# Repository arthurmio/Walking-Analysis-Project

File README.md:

# Walking-Analysis-Project
Projet d'analyse de la marche réalisé par :
  - GOURDON Mathéo
  - MARIANO Arthur 
  - TRIGUI Ianis

Ce projet a été développé dans le cadre du projet "Fil Rouge" en 5ème année à l'ESIEE Paris.  
Ce prototype d'analyse propose une solution d'analyse de la marche sans fil à l'aide d'Arduinos 33 BLE et de capteurs inertiels (BNO005) connectées grâce au protocole BLE (Bluetooth Low Energy). La lecture et l'interprétation des données sont réalisées à l'aide d'une interface sous Python.

# How to use it
Afin d'utiliser correctement le prototype veuillez vous référer à la notice d'utilisation dans le répertoire "Documentation".

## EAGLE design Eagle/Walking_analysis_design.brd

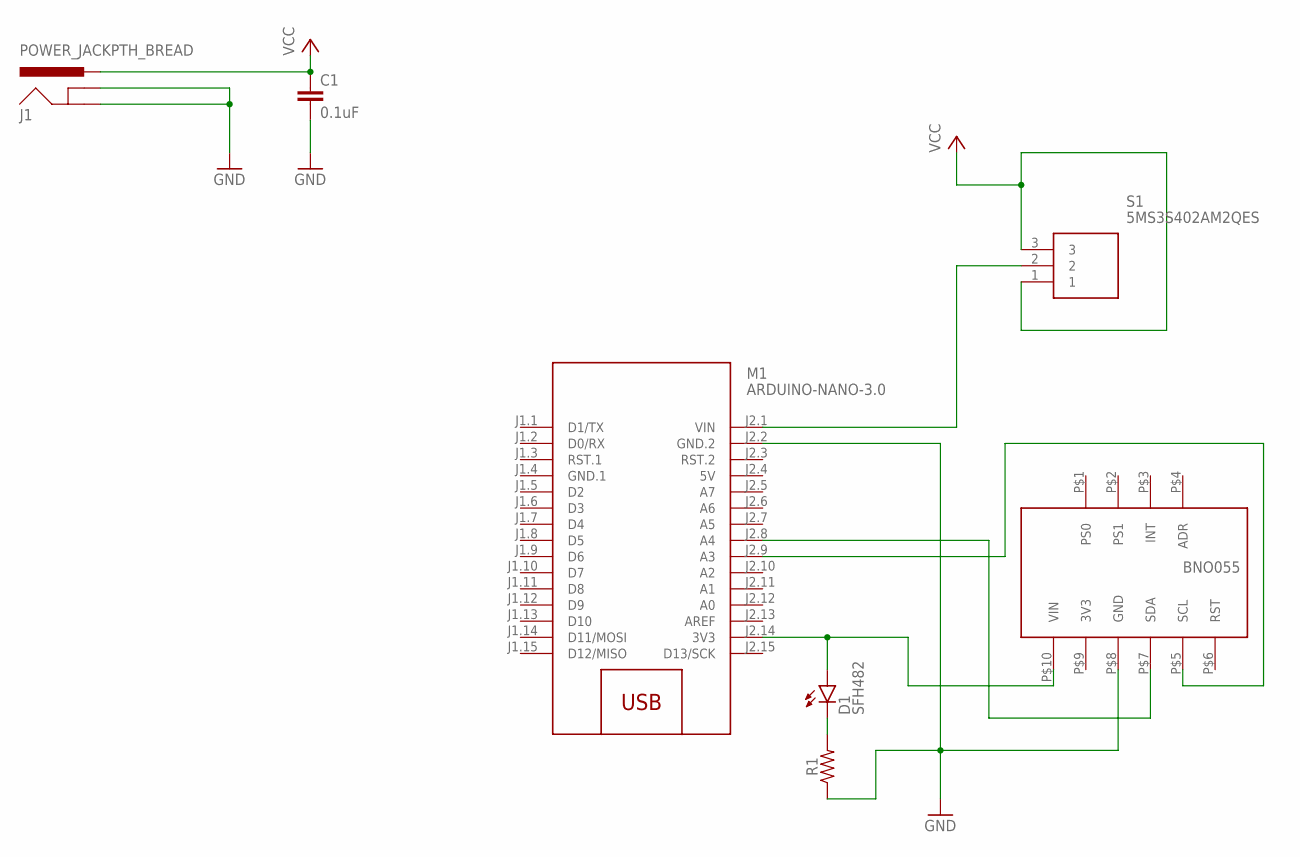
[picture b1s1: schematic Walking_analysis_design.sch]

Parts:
C1: 0.1uF; CAP-PTH-SMALL-KIT
D1: SFH482
J1: POWER_JACKPTH_BREAD; POWER_JACK_PTH_BREAD
M1: ARDUINO-NANO-3.0
R1: AXIAL-0.3
S1: 5MS3S402AM2QES
U$1: BNO055; BNO055_FOOTPRINT

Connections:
3V3: U$1.P$9 (3V3)
5V: M1.J2.4 (5V)
GND: C1.2, J1.GND, J1.GNDBREAK, M1.J2.2 (GND.2), R1.P$1 (1), U$1.P$8 (GND)
GND.1: M1.J1.4 (GND.1)
unnamed: M1.J2.8 (A4), U$1.P$7 (SDA)
unnamed: M1.J2.9 (A3), U$1.P$5 (SCL)
unnamed: D1.A, M1.J2.14 (3V3), U$1.P$10 (VIN)
unnamed: M1.J2.1 (VIN), S1.2
unnamed: D1.K (C), R1.P$2 (2)
VCC: C1.1, J1.PWR, S1.1, S1.3

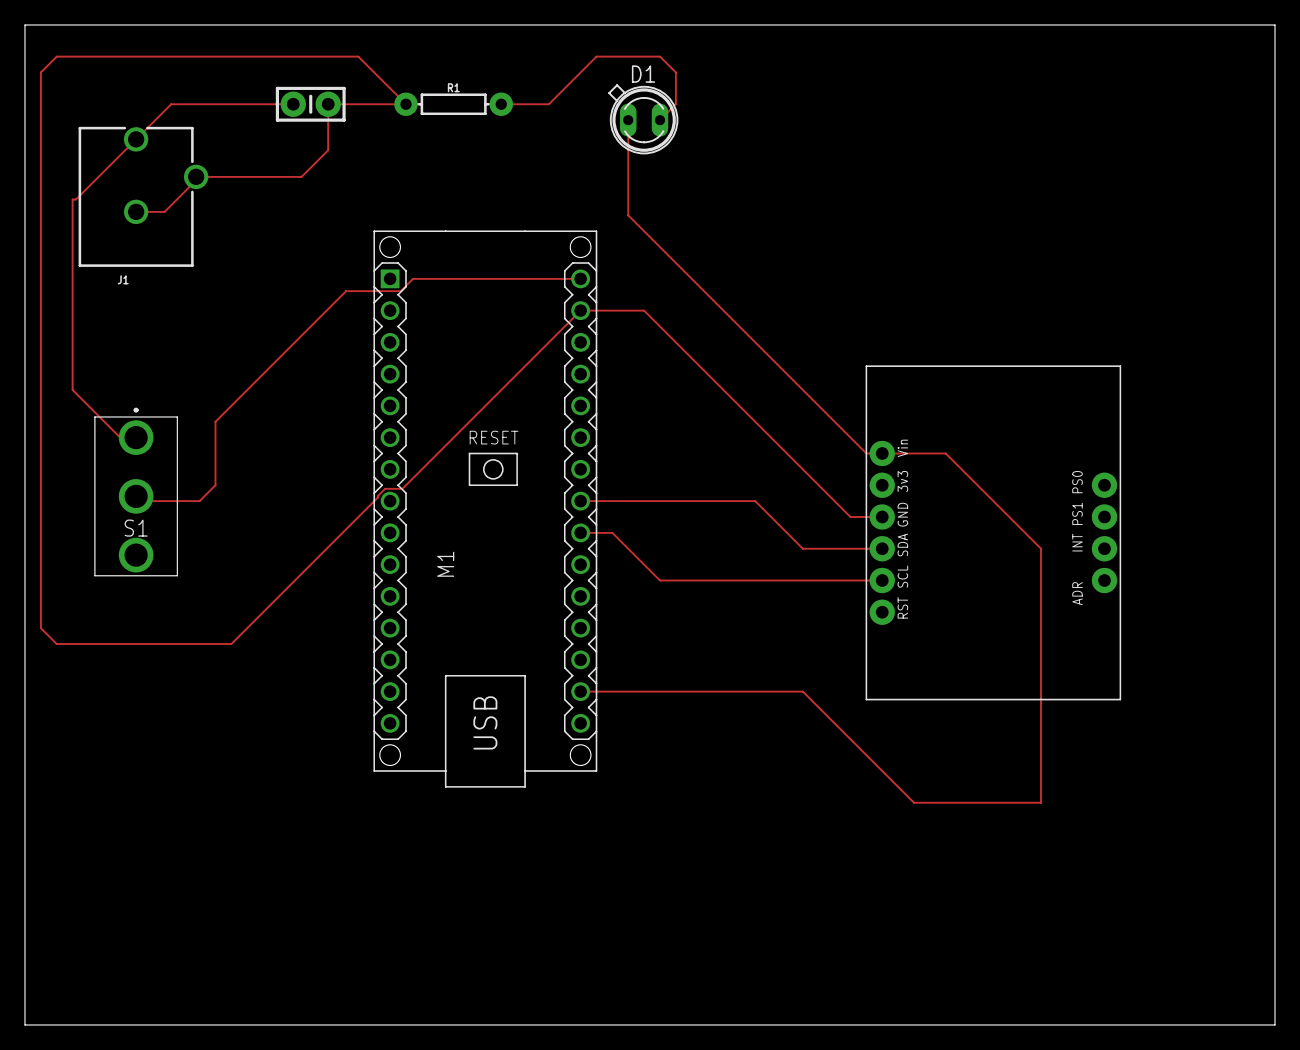
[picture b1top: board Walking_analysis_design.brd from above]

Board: 2 copper layers, 100.0 x 80.0 mm, 7 parts (0 on the bottom side), 7 nets.

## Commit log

2021-01-19 Creation of Arduino and Python repository
2021-01-19 File for git command
2021-03-18 Branch python created for interface
2021-03-18 Decoupage code
2021-03-19 Matplotlib added
2021-03-19 Arduino BLE connection
2021-03-24 Arduino data connected to python
2021-03-24 Correction of BN055_euler for serial interface
2021-03-26 Graphic created for yaw/pitch/roll in real time
2021-03-31 Data saved in a file + plot of this data
2021-03-31 Data save + plot for all arduino
2021-04-02 Update of interface for plot
2021-04-02 Interface with different windows
2021-04-06 Final interface
2021-04-06 Final Arduino files
2021-04-06 Mise à jour README
2021-04-07 Files for PCB design with Eagle
2021-04-07 Presentation orale finale
2021-04-08 3D printing file of the case
2021-04-10 Plot in real time corrected
2021-04-11 Rapport analyse de la marche
2021-04-27 Notice d'utilisation
2021-04-27 Readme updated
2021-04-27 Update Readme 2
2021-04-27 Update Readme 3

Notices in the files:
parts and their libraries:
SparkFun-Capacitors: Licensing: Creative Commons ShareAlike 4.0 International - https://creativecommons.org/licenses/by-sa/4.0
diy-modules: Released under the Creative Commons Attribution 4.0 International License: http://creativecommons.org/licenses/by/4.0
